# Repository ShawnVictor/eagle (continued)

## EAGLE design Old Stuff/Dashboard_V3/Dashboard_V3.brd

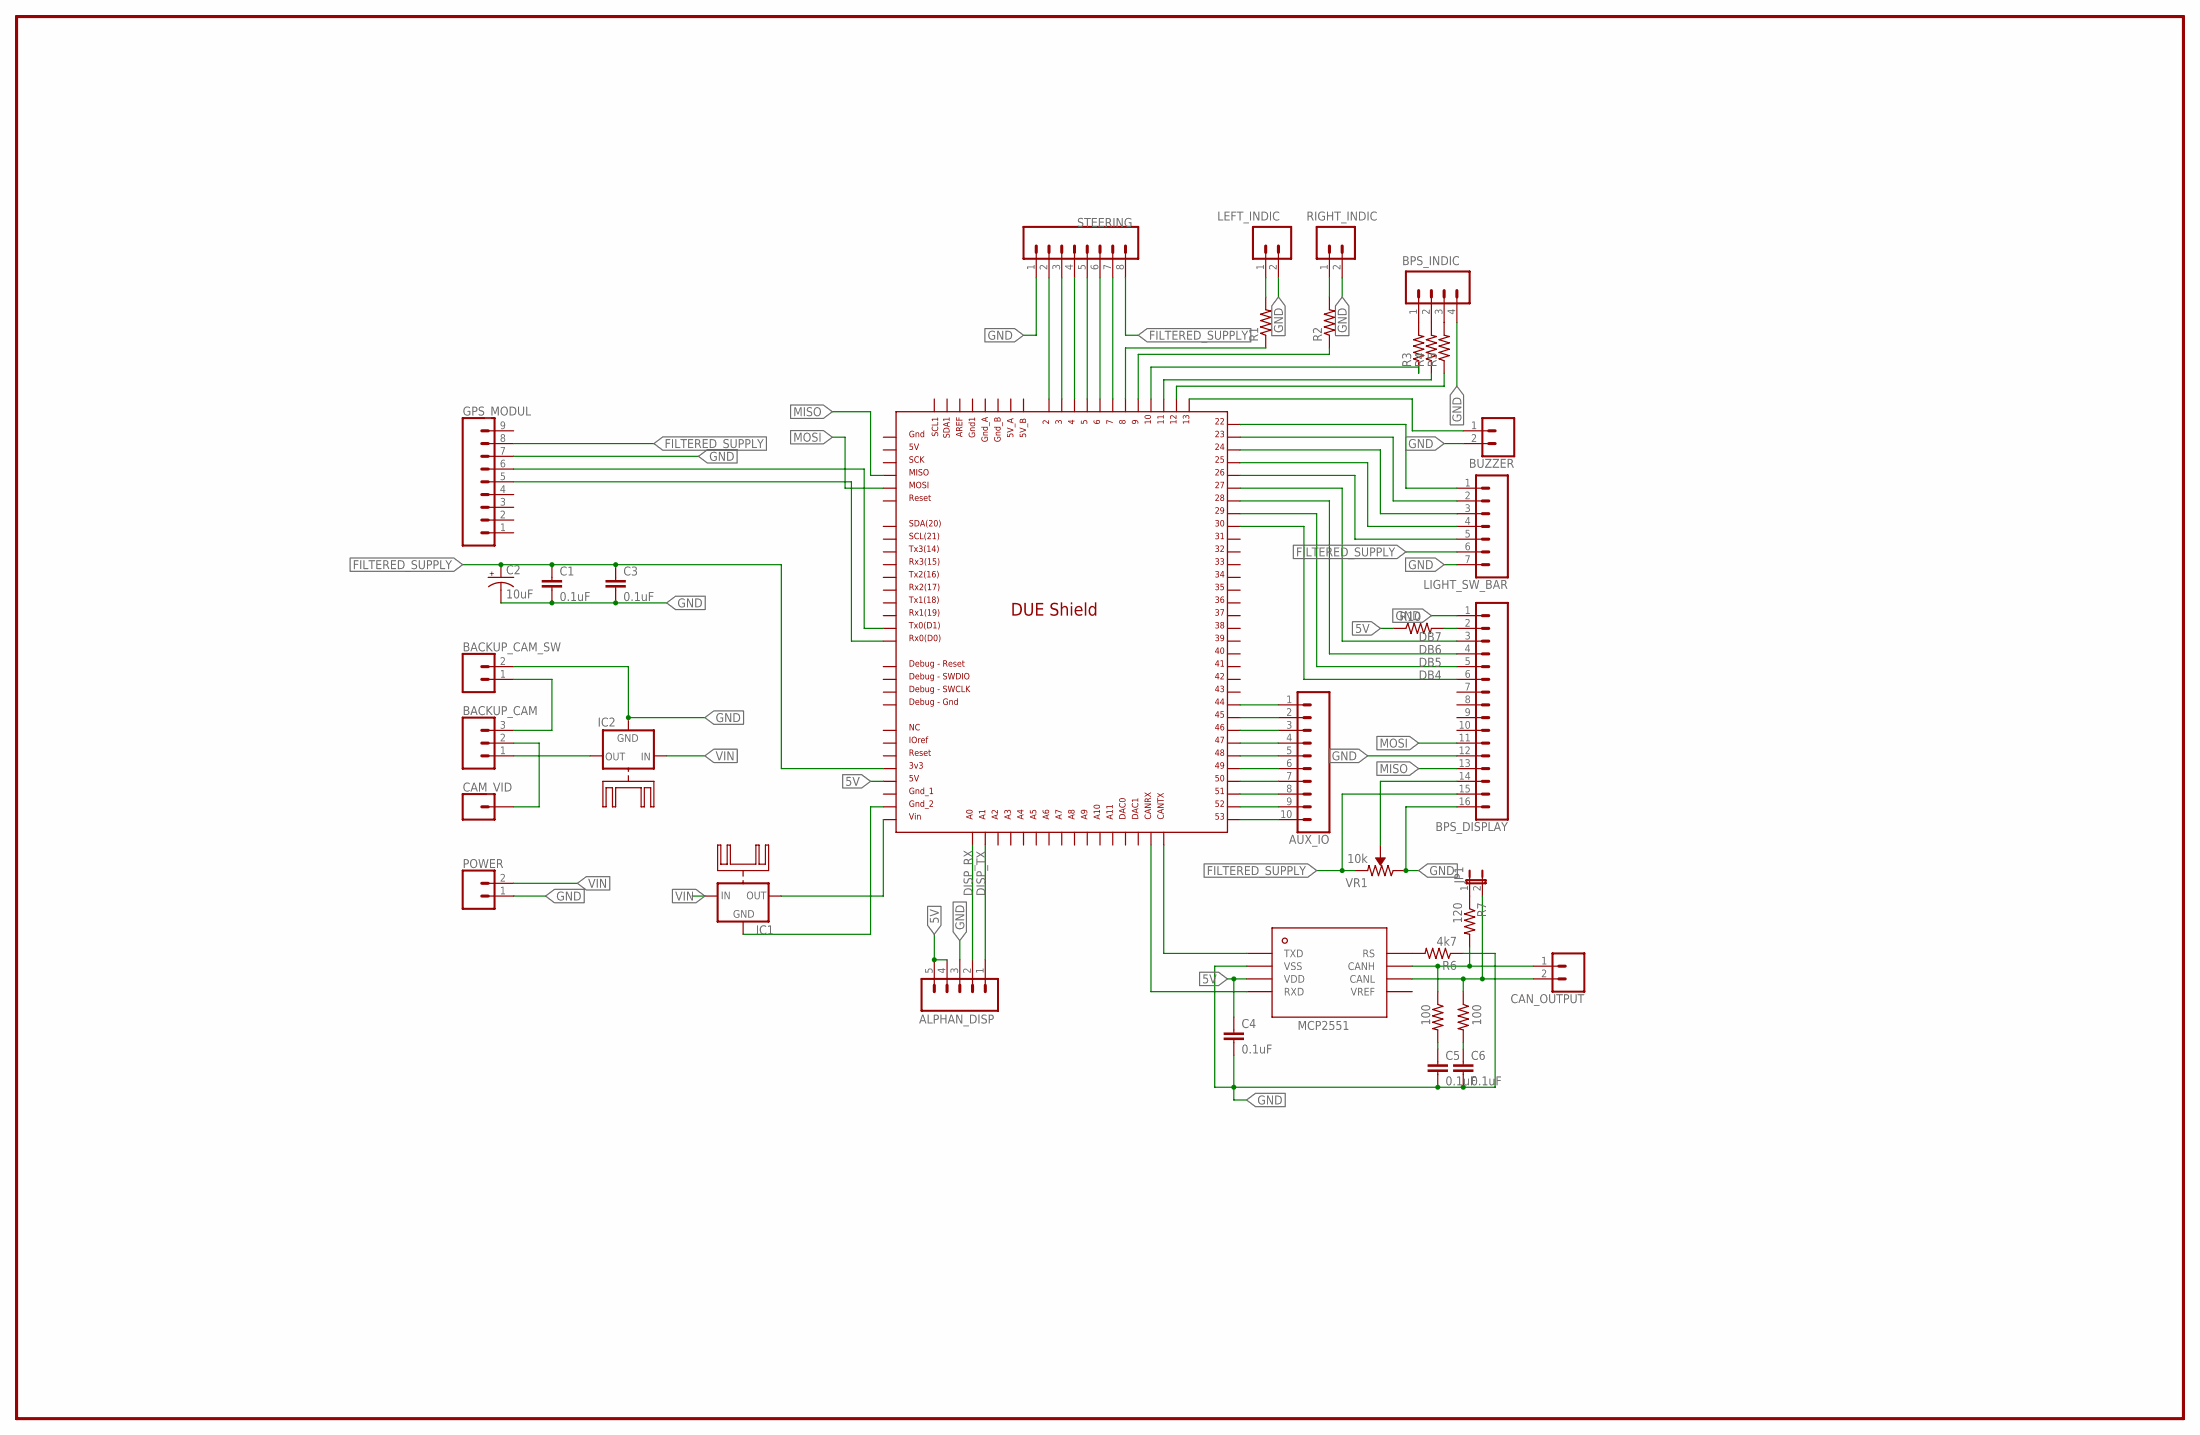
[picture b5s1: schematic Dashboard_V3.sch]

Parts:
ALPHAN_DISP: CONN_05; 1X05
AUX_IO: CONN_10"; 1X10
BACKUP_CAM: CONN_03; 1X03
BACKUP_CAM_SW: CONN_02; 1X02
BPS_DISPLAY: CONN_16; 1X16
BPS_INDIC: CONN_04; 1X04
BUZZER: CONN_02; 1X02
C1, C3, C4, C5, C6: 0.1uF; C2.5-6
C2: 10uF; E5-6
CAM_VID: CONN_01; 1X01
CAN_OUTPUT: CONN_025MM; SCREWTERMINAL-5MM-2
GPS_MODUL: CONN_09; 1X09
IC1, IC2: 78XXH
JP1: JP1E; JP1
LEFT_INDIC: CONN_02; 1X02
LIGHT_SW_BAR: CONN_07; 1X07
POWER: CONN_02; 1X02
R1, R2, R3, R4, R5: R-US_M0805; M0805
R6: 4k7; R0805
R7: 120; R0805
R8, R9: 100; R0805
R10: R-US_R0805; R0805
RIGHT_INDIC: CONN_02; 1X02
STEERING: CONN_08"; 1X08
U$1: DUE(NORMAL)
U$2: MCP2551; SOIC-8
VR1: 10k; TRIMPOT-PTH-3386U

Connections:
5V: ALPHAN_DISP.4, ALPHAN_DISP.5, C4.1, R10.1, U$1.5V, U$2.VDD
CAM_VID: BACKUP_CAM.2, CAM_VID.1
DB4: BPS_DISPLAY.6, U$1.30
DB5: BPS_DISPLAY.5, U$1.29
DB6: BPS_DISPLAY.4, U$1.28
DB7: BPS_DISPLAY.3, U$1.27
DISP_RX: ALPHAN_DISP.2, U$1.A0
DISP_TX: ALPHAN_DISP.1, U$1.A1
FILTERED_SUPPLY: BPS_DISPLAY.15, C1.1, C2.+, C3.1, GPS_MODUL.8, LIGHT_SW_BAR.6, STEERING.8, U$1.3V3, VR1.1 (CCW)
GND: ALPHAN_DISP.3, BACKUP_CAM_SW.2, BPS_DISPLAY.1, BPS_DISPLAY.12, BPS_DISPLAY.16, BPS_INDIC.4, BUZZER.2, C1.2, C2.-, C3.2, C4.2, C5.2, C6.2, GPS_MODUL.7, IC2.GND, LEFT_INDIC.2, LIGHT_SW_BAR.7, POWER.1, R6.1, RIGHT_INDIC.2, STEERING.1, U$2.VSS, VR1.3 (CW)
MISO: BPS_DISPLAY.13, U$1.MISO_ICSP
MOSI: BPS_DISPLAY.11, U$1.MOSI_ICSP
unnamed: IC1.OUT, U$1.VIN
unnamed: IC1.GND, U$1.GND_2
unnamed: BACKUP_CAM.1, IC2.OUT
unnamed: STEERING.2, U$1.2
unnamed: BACKUP_CAM.3, BACKUP_CAM_SW.1
unnamed: STEERING.3, U$1.3
unnamed: STEERING.4, U$1.4
unnamed: STEERING.5, U$1.5
unnamed: STEERING.6, U$1.6
unnamed: STEERING.7, U$1.7
unnamed: LEFT_INDIC.1, R1.2
unnamed: R2.2, RIGHT_INDIC.1
unnamed: R1.1, U$1.8
unnamed: R2.1, U$1.9
unnamed: BPS_INDIC.1, R3.2
unnamed: BPS_INDIC.2, R4.2
unnamed: BPS_INDIC.3, R5.2
unnamed: R3.1, U$1.10
unnamed: R4.1, U$1.11
unnamed: R5.1, U$1.12
unnamed: U$1.CANTX, U$2.TXD
unnamed: U$1.CANRX, U$2.RXD
unnamed: R6.2, U$2.RS
unnamed: JP1.1, R7.1
unnamed: CAN_OUTPUT.1, R7.2, R8.1, U$2.CANH
unnamed: CAN_OUTPUT.2, JP1.2, R9.1, U$2.CANL
unnamed: C5.1, R8.2
unnamed: C6.1, R9.2
unnamed: BUZZER.1, U$1.13
unnamed: GPS_MODUL.6, U$1.TX0
unnamed: GPS_MODUL.5, U$1.RX0
unnamed: BPS_DISPLAY.2, R10.2
unnamed: BPS_DISPLAY.14, VR1.2 (WIPER)
unnamed: LIGHT_SW_BAR.1, U$1.22
unnamed: LIGHT_SW_BAR.2, U$1.23
unnamed: LIGHT_SW_BAR.3, U$1.24
unnamed: LIGHT_SW_BAR.4, U$1.25
unnamed: LIGHT_SW_BAR.5, U$1.26
unnamed: AUX_IO.10, U$1.53
unnamed: AUX_IO.9, U$1.52
unnamed: AUX_IO.8, U$1.51
unnamed: AUX_IO.7, U$1.50
unnamed: AUX_IO.6, U$1.49
unnamed: AUX_IO.5, U$1.48
unnamed: AUX_IO.4, U$1.47
unnamed: AUX_IO.3, U$1.46
unnamed: AUX_IO.2, U$1.45
unnamed: AUX_IO.1, U$1.44
VIN: IC1.IN, IC2.IN, POWER.2

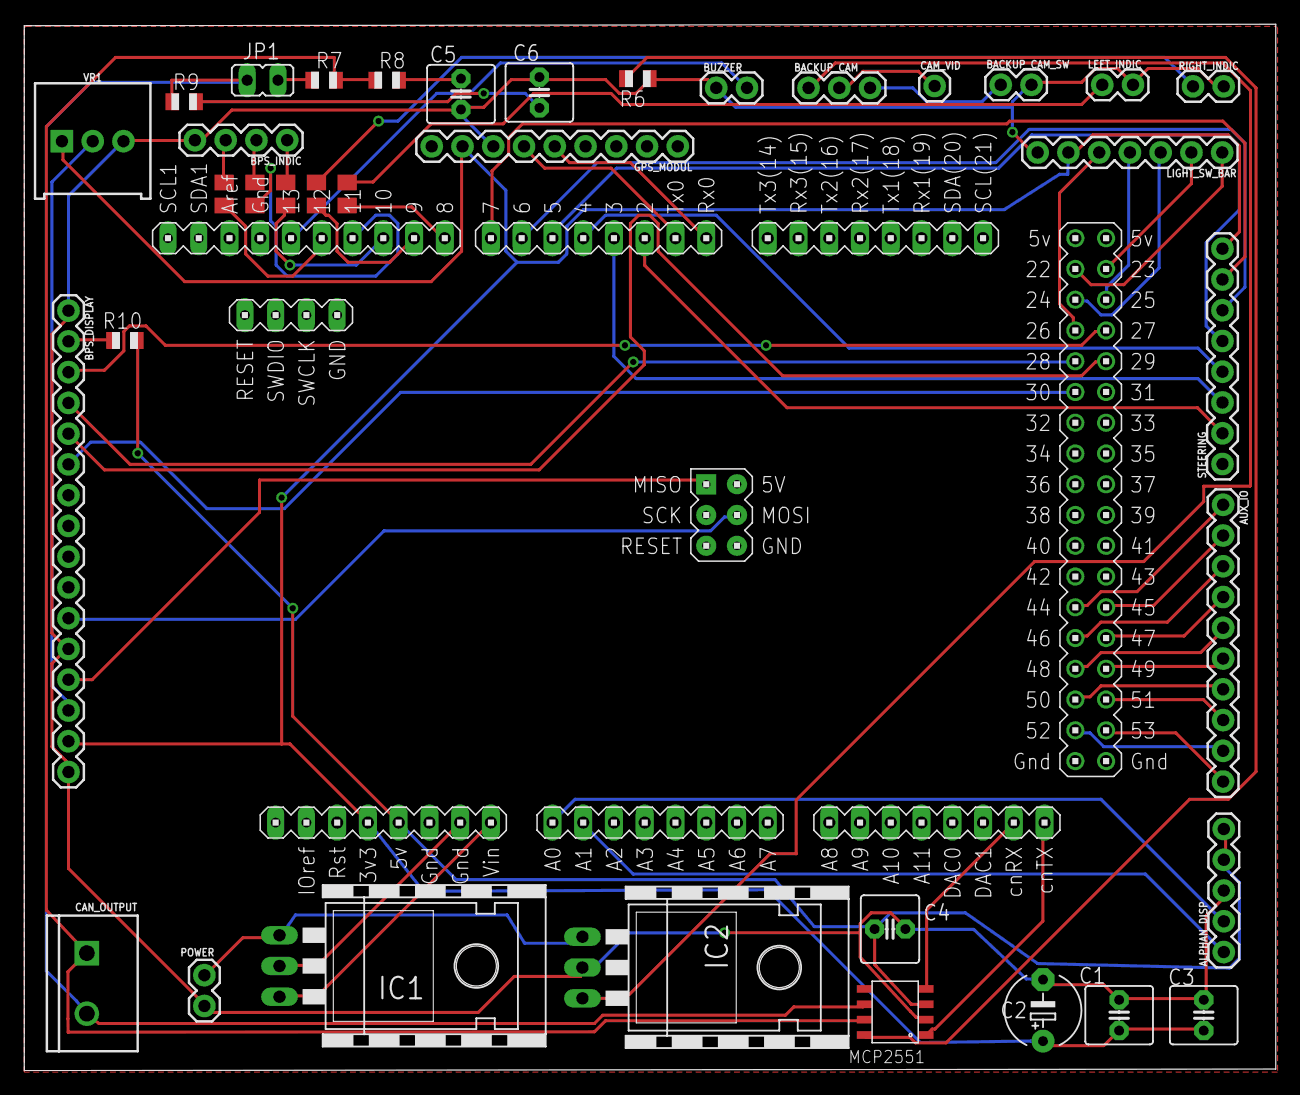
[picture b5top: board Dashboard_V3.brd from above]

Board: 2 copper layers, 103.4 x 86.4 mm, 37 parts (0 on the bottom side), 61 nets.
